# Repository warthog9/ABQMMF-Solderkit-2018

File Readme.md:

# 2018 Albuquerque Mini-Maker Faire Soldering Kit

This is the 2018 Albuquerque Mini-Maker Faire soldering kit, it's intended
to be a useful item that people will actually use as opposed to just a
series of blinky LEDs.  It makes use of the NodeMCU, which is based on the
ESP8266, a microcontroller that has wifi capabilities.

## Out of the box
Out of the box the kit will include the following things:
* PCB of the Cloud Sun variety (pictured below)
* 2x 15-pin, female, 0.1" headers
* 2x 4-pin, female, 0.1" headers
* 1x 1K Ohm resistor
* 1x 5mm Red LED
* 1x Diode
* 1x 3-AAA battery pack
* 1x Red button (intended to go in the middle - but doesn't matter)
* 4x Black buttons (electrically identical to the red)
* 1x 2x10-pin, male, 0.1" header
* 1x I2C, 4-pin, OLED screen
* 1x BME280, I2C 4-pin, breakout board
* 1x NodeMCU v2 (CP2102 USB chip type)

The board will boot up, once soldered up, and will show the following information on the OLED screen:
* Battery level (upper right corner)
* Temperature
* Barometric pressure
* Relative humidity

The buttons do the following:
* Top: Increases OLED screen brightness
* Bottom: Decreases OLED screen brightness
* Middle: Toggles temperature readout between Celsius and Fahrenheit (Default Fahrenheit)
* Left: Toggles between condensed or extended text on the OLED screen
* Right: Will toggle the two extra LEDs on the ESP12e/f module and the NodeMCU itself

The NodeMCU has been pre-loaded with [MicroPython](https://micropython.org), which is a slimmed down version of Python 3 intended for micro-controllers.  This is greater for people to start with, and you can find some basic tutorials on how to interact with the board quickly here:

* https://docs.micropython.org/en/latest/esp8266/esp8266/tutorial/intro.html
* https://github.com/unreproducible/tinysnakes

Wifi is disabled for this demo via [boot.py](https://github.com/warthog9/ABQMMF-Solderkit-2018/blob/master/src/boot.py), but can be easily changed and/or re-enabled.

Files were uploaded to the board using [ampy](https://github.com/adafruit/ampy)

## Schematic

Full schematic is here: [Schematic PDF](abqmmf2018-schematic.pdf)

### PCB outline

### Prototype built up

### Raw PCBs (prototypes)

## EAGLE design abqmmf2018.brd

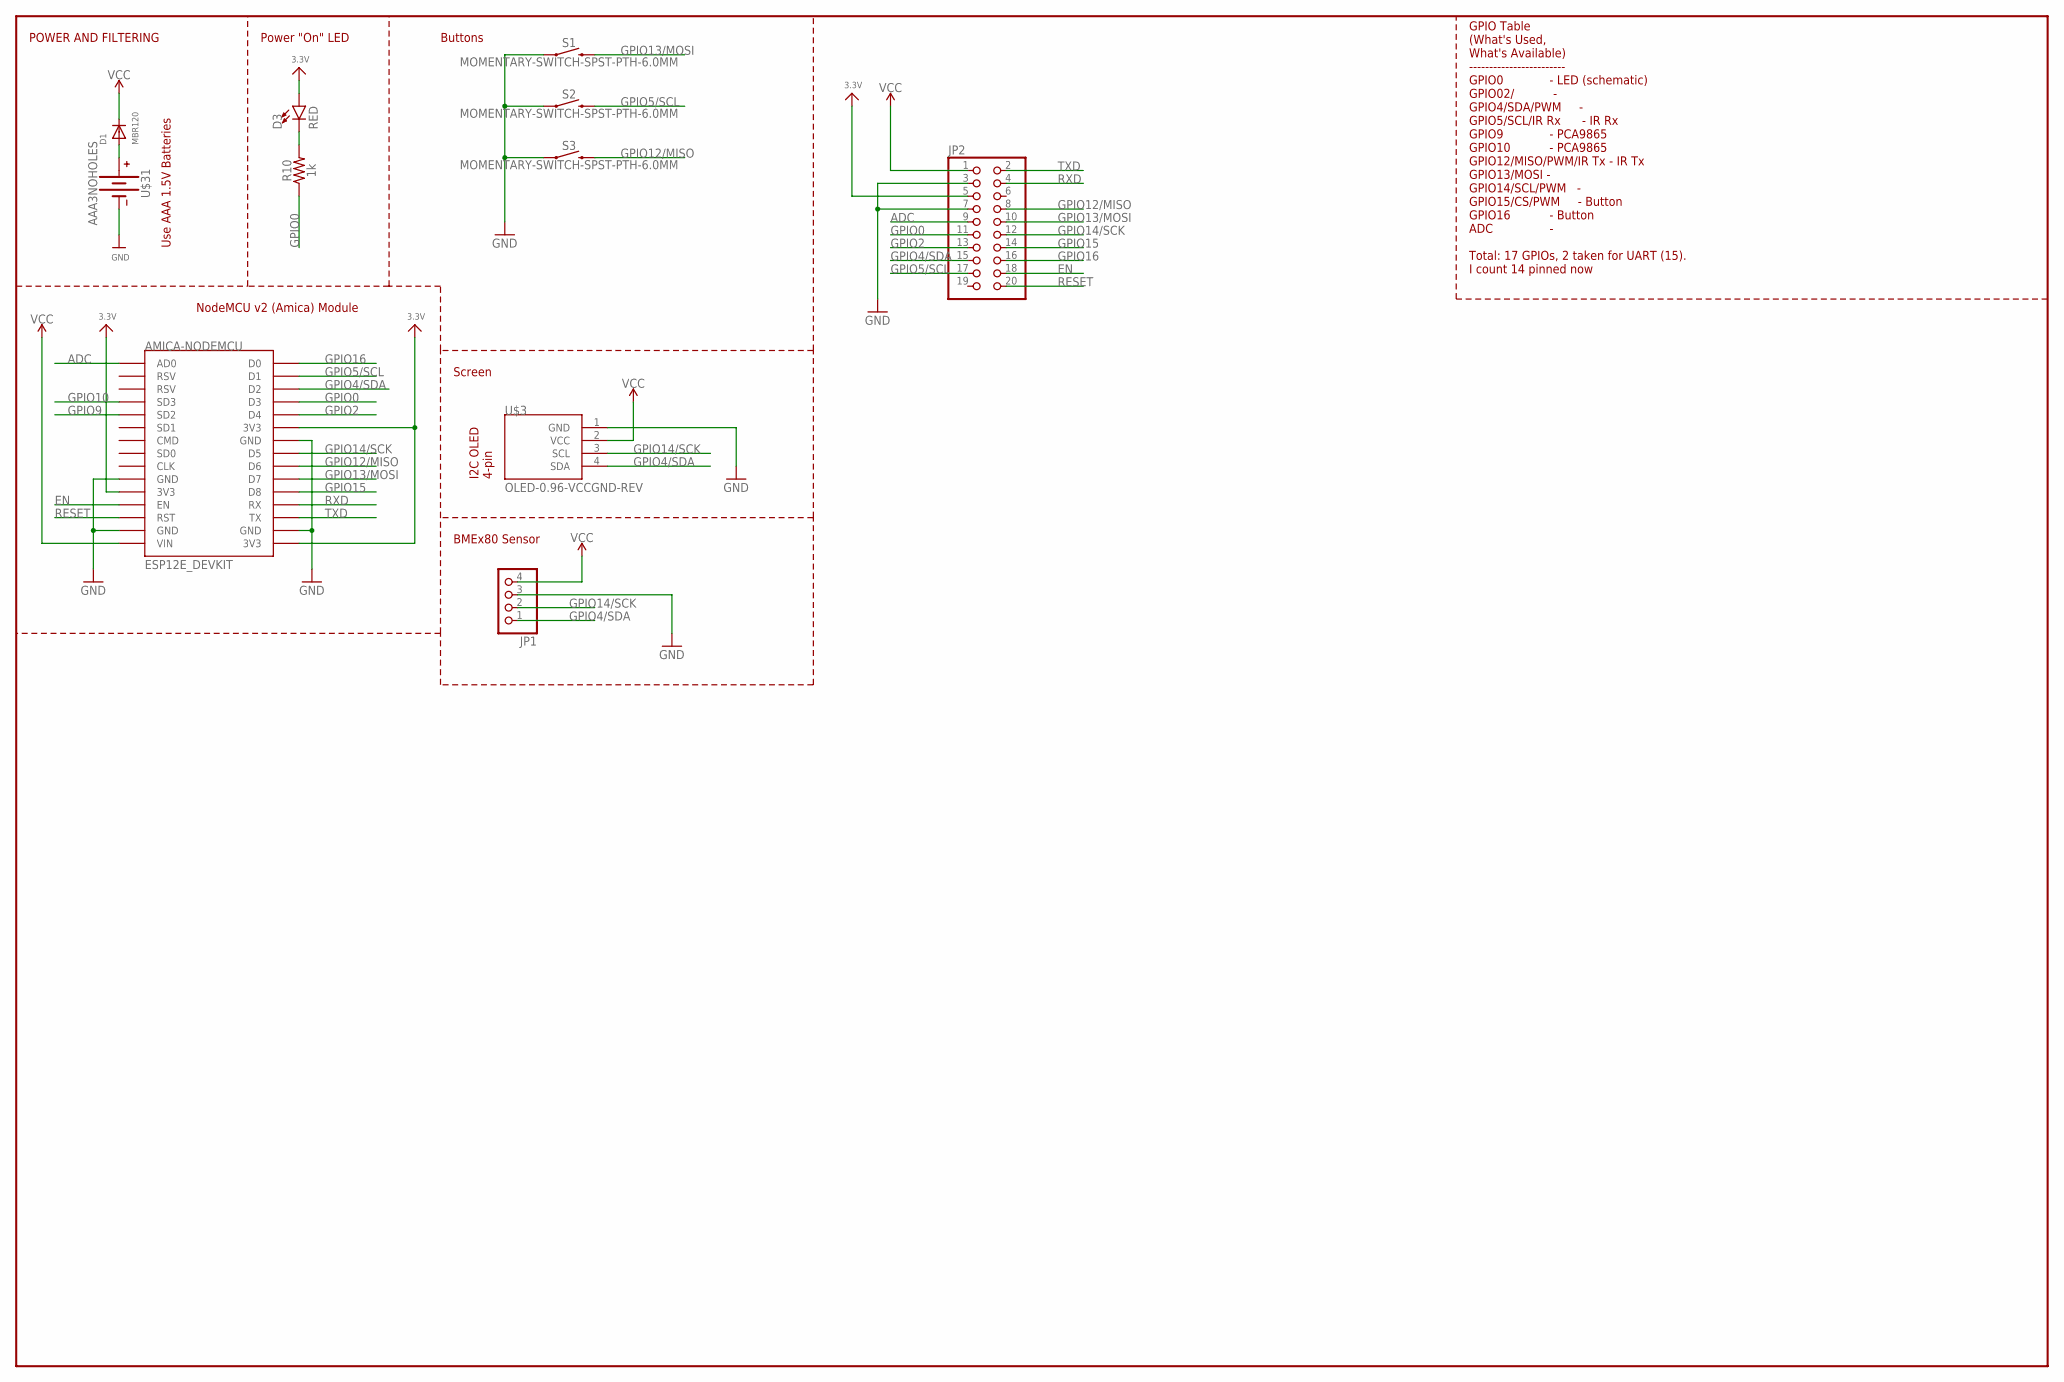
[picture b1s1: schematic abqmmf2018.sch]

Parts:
AMICA-NODEMCU: ESP12E_DEVKIT
D1: MBR120; DO-1N4148
D3: RED; LED_5MM
JP1: PINHD-1X4; 1X04
JP2: PINHD-2X10; 2X10
R10: 1k; AXIAL-0.3
S1, S2, S3: MOMENTARY-SWITCH-SPST-PTH-6.0MM; TACTILE_SWITCH_PTH_6.0MM
U$3: OLED-0.96-VCCGND-REV; OLED-I2C-4PIN-VCCGND-REV
U$31: AAA3NOHOLES; AAA3-NOHOLES

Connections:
3.3V: AMICA-NODEMCU.3V3@0 (3V3), AMICA-NODEMCU.3V3@1 (3V3), AMICA-NODEMCU.3V3@2 (3V3), D3.A, JP2.5
ADC: AMICA-NODEMCU.AD0, JP2.9
EN: AMICA-NODEMCU.EN, JP2.18
GND: AMICA-NODEMCU.GND@0 (GND), AMICA-NODEMCU.GND@1 (GND), AMICA-NODEMCU.GND@2 (GND), AMICA-NODEMCU.GND@3 (GND), JP1.3, JP2.3, JP2.7, S1.1, S2.1, S3.1, U$3.1 (GND), U$31.NEG (-)
GPIO0: AMICA-NODEMCU.D3, JP2.11, R10.P$1 (1)
GPIO2: AMICA-NODEMCU.D4, JP2.13
GPIO4/SDA: AMICA-NODEMCU.D2, JP1.1, JP2.15, U$3.4 (SDA)
GPIO5/SCL: AMICA-NODEMCU.D1, JP2.17, S2.3 (2)
GPIO9: AMICA-NODEMCU.SD2
GPIO10: AMICA-NODEMCU.SD3
GPIO12/MISO: AMICA-NODEMCU.D6, JP2.8, S3.3 (2)
GPIO13/MOSI: AMICA-NODEMCU.D7, JP2.10, S1.3 (2)
GPIO14/SCK: AMICA-NODEMCU.D5, JP1.2, JP2.12, U$3.3 (SCL)
GPIO15: AMICA-NODEMCU.D8, JP2.14
GPIO16: AMICA-NODEMCU.D0, JP2.16
unnamed: D1.A, U$31.POS (+)
unnamed: D3.K (C), R10.P$2 (2)
RESET: AMICA-NODEMCU.RST, JP2.20
RXD: AMICA-NODEMCU.RX, JP2.4
TXD: AMICA-NODEMCU.TX, JP2.2
VCC: AMICA-NODEMCU.VIN, D1.C, JP1.4, JP2.1, U$3.2 (VCC)

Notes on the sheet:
POWER AND FILTERING
Power "On" LED
NodeMCU v2 (Amica) Module
GPIO Table (What's Used, What's Available) ------------------------ GPIO0 - LED (schematic) GPIO02/ - GPIO4/SDA/PWM - GPIO5/SCL/IR Rx - IR Rx GPIO9 - PCA9865 GPIO10 - PCA9865 GPIO12/MISO/PWM/IR Tx - IR Tx GPIO13/MOSI - GPIO14/SCL/PWM - GPIO15/CS/PWM - Button GPIO16 - Button ADC - Total: 17 GPIOs, 2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
Buttons
Use AAA 1.5V Batteries
Screen
BMEx80 Sensor

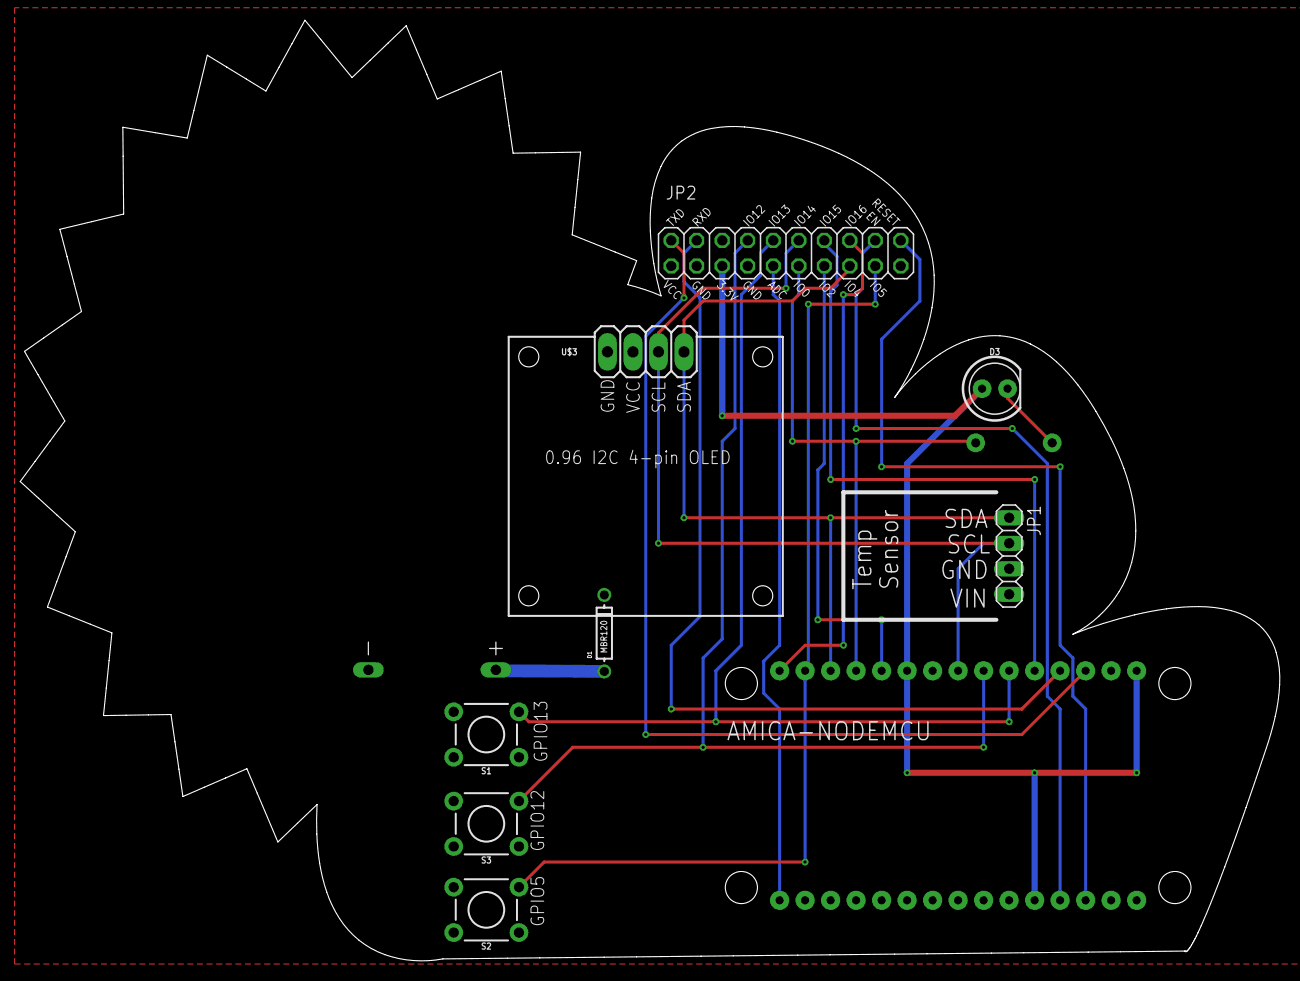
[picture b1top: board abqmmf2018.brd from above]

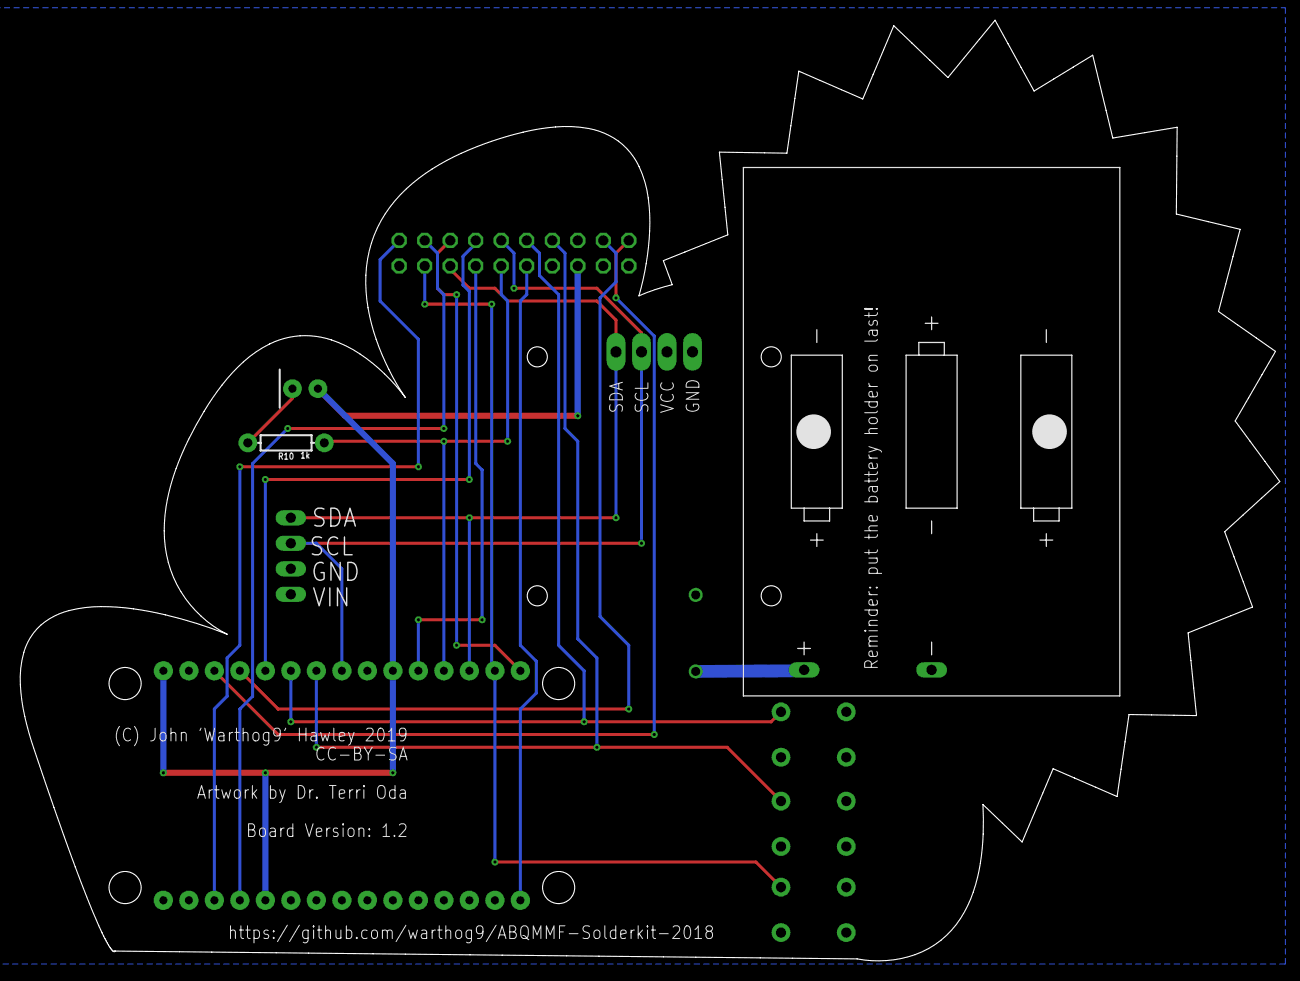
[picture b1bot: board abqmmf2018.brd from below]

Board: 2 copper layers, 125.5 x 93.7 mm, 11 parts (2 on the bottom side), 19 nets.

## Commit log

2018-03-19 Adding the 2018 prototype board files, this is a completed board
2018-03-19 Adding prototype gerbers
2018-03-19 Adding additional Schematic pdf and board picture
2018-03-19 Adding gerbers zip file
2018-03-28 Moving Screen & Sensor, Remove ADC Resistor
    Moving the Sensor more right since it's smaller than I had
    somewhat expected, so that's nice. Moved the screen so that
    it's more inside the cloud.
    Obviously had to do some rerouting to accomodate. Like it a
    little better anyway.
    Also removed the ADC voltage divider resistor. Turns out
2018-04-21 BRD: Fixing Typo next to up button - GPIO13
    I had typoed on the GPIO# next to the Up button
    I had put 'GPIO18', should be 'GPIO13' - fixed.
2018-04-21 Button GPIO15 -> GPIO5
    GPIO15 is apparently always pulled low due
    to boot things (yay), so switching to GPIO5
    to work around it.
2018-04-21 BRD: minor re-routing on gpio5 button
2018-04-21 BRD: cleaning up the DRCs
    This is all because of the PCBWay logo placement
2018-04-21 Adding the tDocu and bDocu to silkscreen layer
    The extra outline information for the Nodemcu
    is in the docu layers, figured it's easier to
    just add those to the cam then to re-do the part
    so that folks can see which way around it's supposed
    to go
2018-04-21 BRD: moving resistor value info to tPlace
    mainly so that this shows up on the silkscreen
2018-04-21 BRD: something got unrotated?
2018-04-21 Adding BOMs
2018-04-21 Source Code: Initial commit, this is what is shipped on the 2018 kits
    This adds a git submodule for the bme280 so we can track that,
    a quick make file for the bme280.mpy (this is needed to keep ram
    usage down), and some extra git ignores.
    I'm throwing in the shell script I used to flash the boards, mostly
    as an example of how to flash the boards - not intending it to be a
    definitive example
2018-04-21 Adding some solid starting documentation for people to stumble on
2019-03-13 Remove accidental double reference
    S2, Pad 3 was accidentally assigned to both GPIO15 and GPIO5/SCL
    Removing GPIO15 since 5 is what's actually routed
2019-03-13 Removing Buttons for GPIO9/10
    These are basically unusable on a certain portion of NodeMCUs,
    so removing them entirely
2019-03-13 Removing GPIO9/10 from expansion header
    These are unusable pins on enough NodeMCUs I'm going to go ahead
    and remove the pins in the general sense
2019-03-13 Use the 0.96in OLED pinout that's got vcc/gnd reversed
2019-03-23 Adjusting the Silkscren, bumping version to 1.2, (c) to 2019
2019-03-23 Fix Silkscreen for down button, to GPIO5 from GPIO15
2019-03-23 Cleaning up DRC issues
2019-03-23 Updating the Schematic to reflect the changes
2019-03-23 BOM changes to reflect the now missing 2 buttons
2019-03-23 Removing the Left and Right buttons since they are no longer used
2019-03-23 Move the gerbers.zip out of the zip directory
2019-03-23 Updating Gerbers
2019-05-06 Fixing gerbers

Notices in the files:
abqmmf2018.brd:
CC-BY-SA
parts and their libraries:
SparkFun-LED: Licensing: Creative Commons ShareAlike 4.0 International - https://creativecommons.org/licenses/by-sa/4.0
microbuilder: This work is placed in the public domain, and may be freely used for commercial and non-commercial work with the following conditions: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
